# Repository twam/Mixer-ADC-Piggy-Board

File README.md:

Mixer-ADC-Piggy-Board
===

This repository is part of the USB audio mixer project described on https://www.twam.info/general/building-a-custom-usb-audio-mixer.

It is currently not used in the final design.

## License

[![CC BY-SA 4.0][cc-by-sa-shield]][cc-by-sa]

This work is licensed under a [Creative Commons Attribution-NonCommercial-ShareAlike 4.0 International License][cc-by-sa].

[![CC BY-SA 4.0][cc-by-sa-image]][cc-by-sa]

[cc-by-sa]: http://creativecommons.org/licenses/by-nc-sa/4.0/
[cc-by-sa-image]: https://licensebuttons.net/l/by-nc-sa/4.0/88x31.png
[cc-by-sa-shield]: https://img.shields.io/badge/License-CC%20BY--NC--SA%204.0-lightgrey.svg

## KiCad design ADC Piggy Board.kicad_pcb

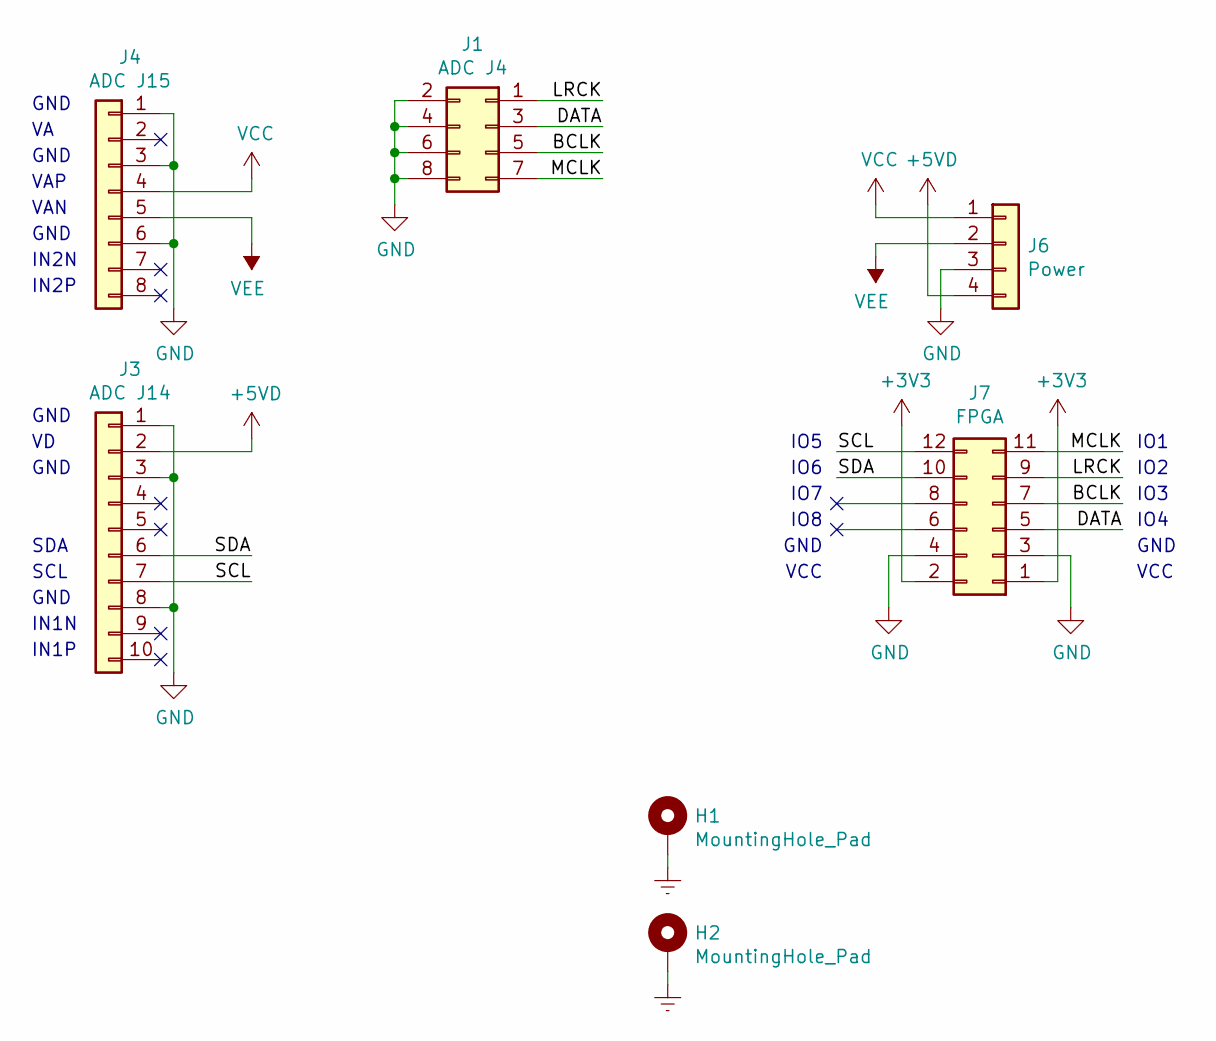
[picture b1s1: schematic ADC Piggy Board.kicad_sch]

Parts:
H1, H2: MountingHole_Pad; MountingHole_3.2mm_M3_DIN965_Pad
J1: ADC J4; PinSocket_2x04_P2.54mm_Vertical
J3: ADC J14; PinSocket_1x10_P2.54mm_Vertical
J4: ADC J15; PinSocket_1x08_P2.54mm_Vertical
J6: Power; JST_VH_B4PS-VH_1x04_P3.96mm_Horizontal
J7: FPGA; PinHeader_2x06_P2.54mm_Horizontal

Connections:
+3V3: J7.1, J7.2
+5VD: J3.2, J6.4
/BCLK: J1.5, J7.7
/DATA: J1.3, J7.5
/IRQ: J7.8
/LRCK: J1.1, J7.9
/MCLK: J1.7, J7.11
/Mute: J7.6
/SCL: J3.7, J7.12
/SDA: J3.6, J7.10
Earth: H1.1, H2.1
GND: J1.2, J1.4, J1.6, J1.8, J3.1, J3.3, J3.8, J4.1, J4.3, J4.6, J6.3, J7.3, J7.4
VCC: J4.4, J6.1
VEE: J4.5, J6.2

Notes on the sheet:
IN2P
VAP
IO1
IO7
GND
IN1N
VAN
SDA
IO8
VCC
IO4
IO5
SCL
IN2N
IO2
IO3
IN1P
IO6

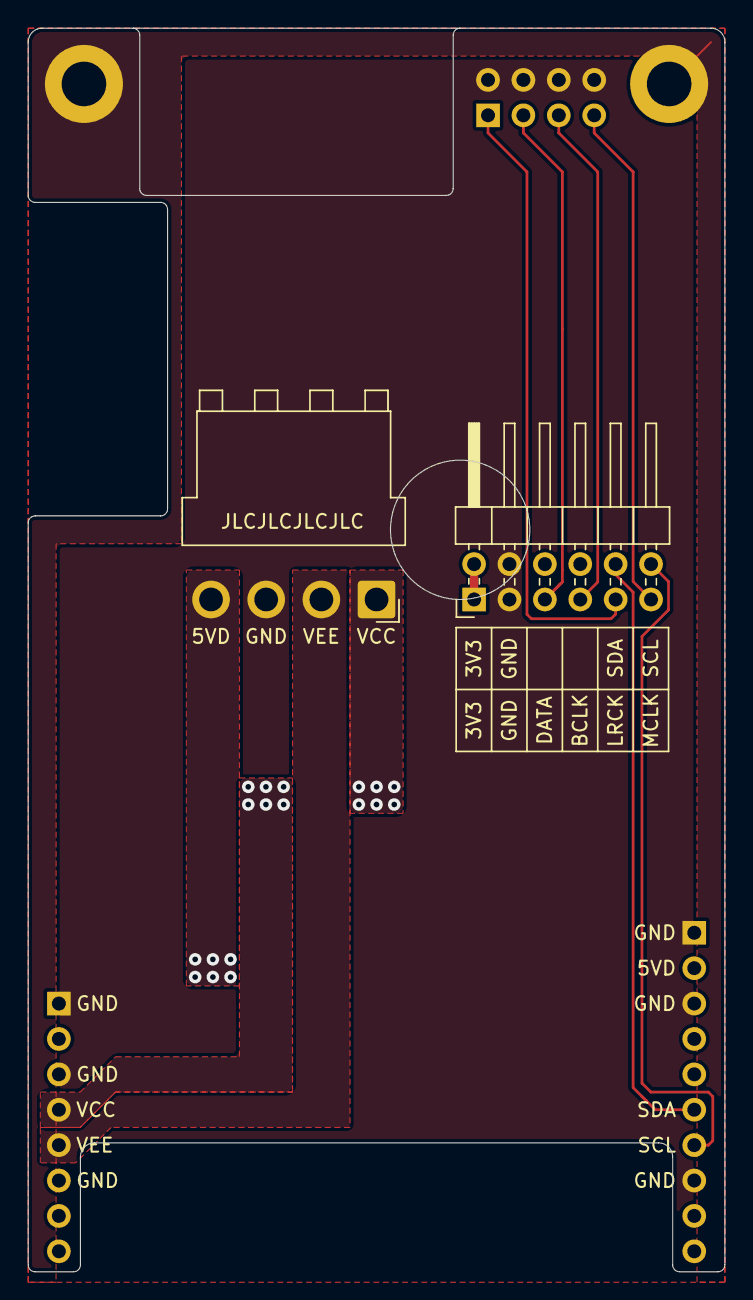
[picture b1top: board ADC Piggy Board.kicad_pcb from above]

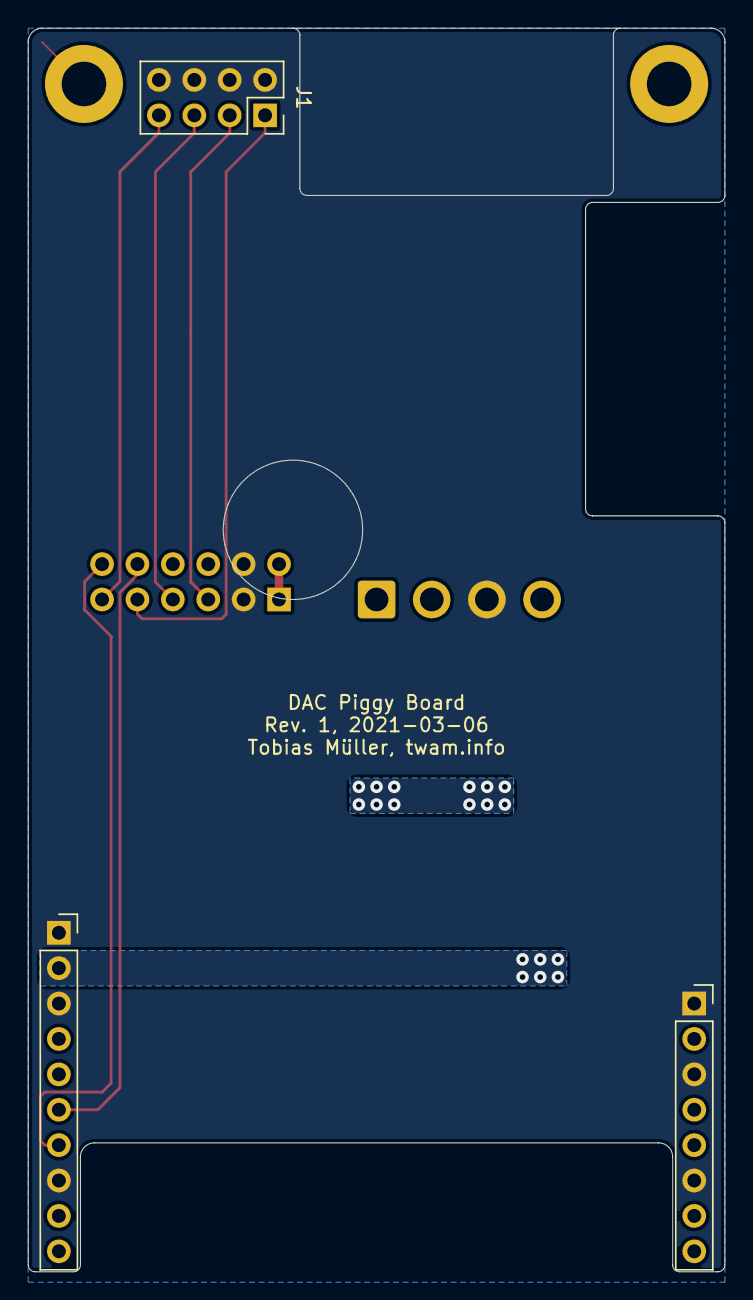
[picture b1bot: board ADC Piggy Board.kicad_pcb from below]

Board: 2 copper layers, 50.0 x 89.2 mm, 7 parts (3 on the bottom side), 12 nets.

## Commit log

2022-01-07 Initial commit, Rev. 1
2022-01-07 Update to KiCad 6
2022-01-08 Add README
